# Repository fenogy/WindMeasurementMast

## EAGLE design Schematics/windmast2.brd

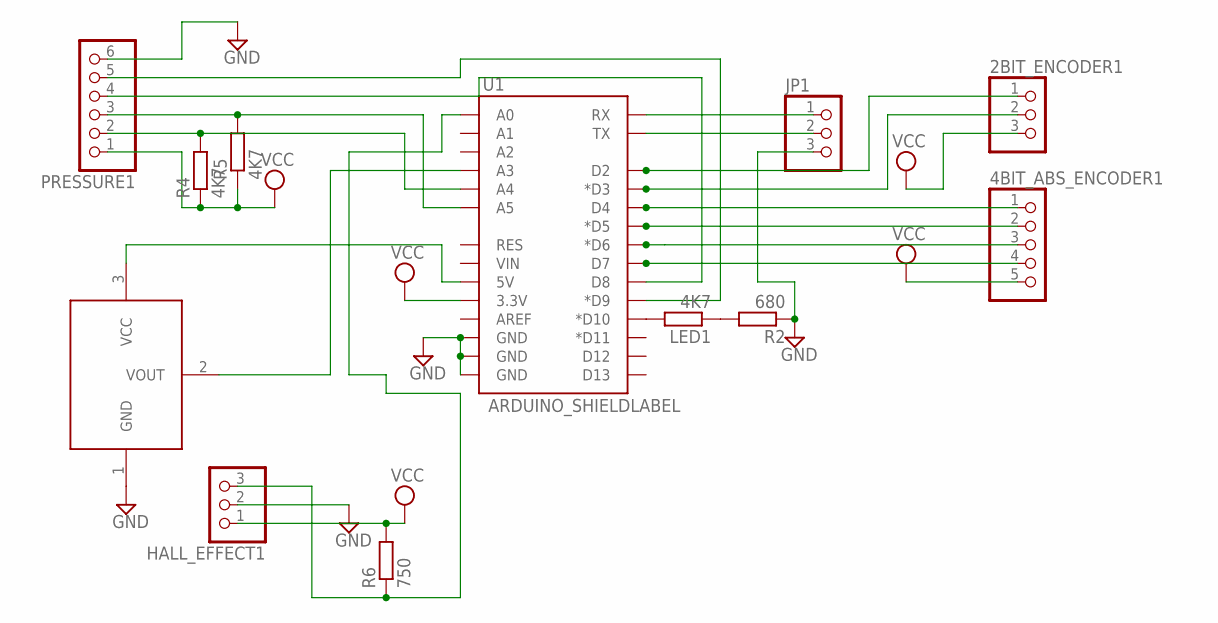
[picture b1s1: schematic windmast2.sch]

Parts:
2BIT_ENCODER1: PINHD-1X3; 1X03
4BIT_ABS_ENCODER1: PINHD-1X5; 1X05
HALL_EFFECT1: PINHD-1X3; 1X03
IC1: LM35; TO92
JP1: PINHD-1X3; 1X03
LED1: 4K7; R0805
PRESSURE1: PINHD-1X6; 1X06
R2: 680; R0805
R4, R5: 4K7; R0805
R6: 750; R0805
U1: ARDUINO_SHIELDLABEL; DUEMILANOVE_SHIELD

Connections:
GND: HALL_EFFECT1.2, IC1.1 (GND), JP1.3, PRESSURE1.6, R2.1, U1.GND@0 (GND), U1.GND@1 (GND), U1.GND@2 (GND)
unnamed: IC1.2 (VOUT), U1.A3
unnamed: IC1.3 (VCC), U1.5V
unnamed: LED1.2, U1.D10 (*D10)
unnamed: LED1.1, R2.2
unnamed: JP1.1, U1.RX
unnamed: JP1.2, U1.TX
unnamed: PRESSURE1.2, R4.2, U1.A4
unnamed: PRESSURE1.3, R5.2, U1.A5
unnamed: PRESSURE1.4, U1.D8
unnamed: PRESSURE1.5, U1.D9 (*D9)
unnamed: 2BIT_ENCODER1.1, U1.D2
unnamed: 2BIT_ENCODER1.2, U1.D3 (*D3)
unnamed: 4BIT_ABS_ENCODER1.1, U1.D4
unnamed: 4BIT_ABS_ENCODER1.2, U1.D5 (*D5)
unnamed: 4BIT_ABS_ENCODER1.3, U1.D6 (*D6)
unnamed: 4BIT_ABS_ENCODER1.4, U1.D7
unnamed: HALL_EFFECT1.3, R6.1, U1.A0
VCC: 2BIT_ENCODER1.3, 4BIT_ABS_ENCODER1.5, HALL_EFFECT1.1, PRESSURE1.1, R4.1, R5.1, R6.2, U1.3.3V

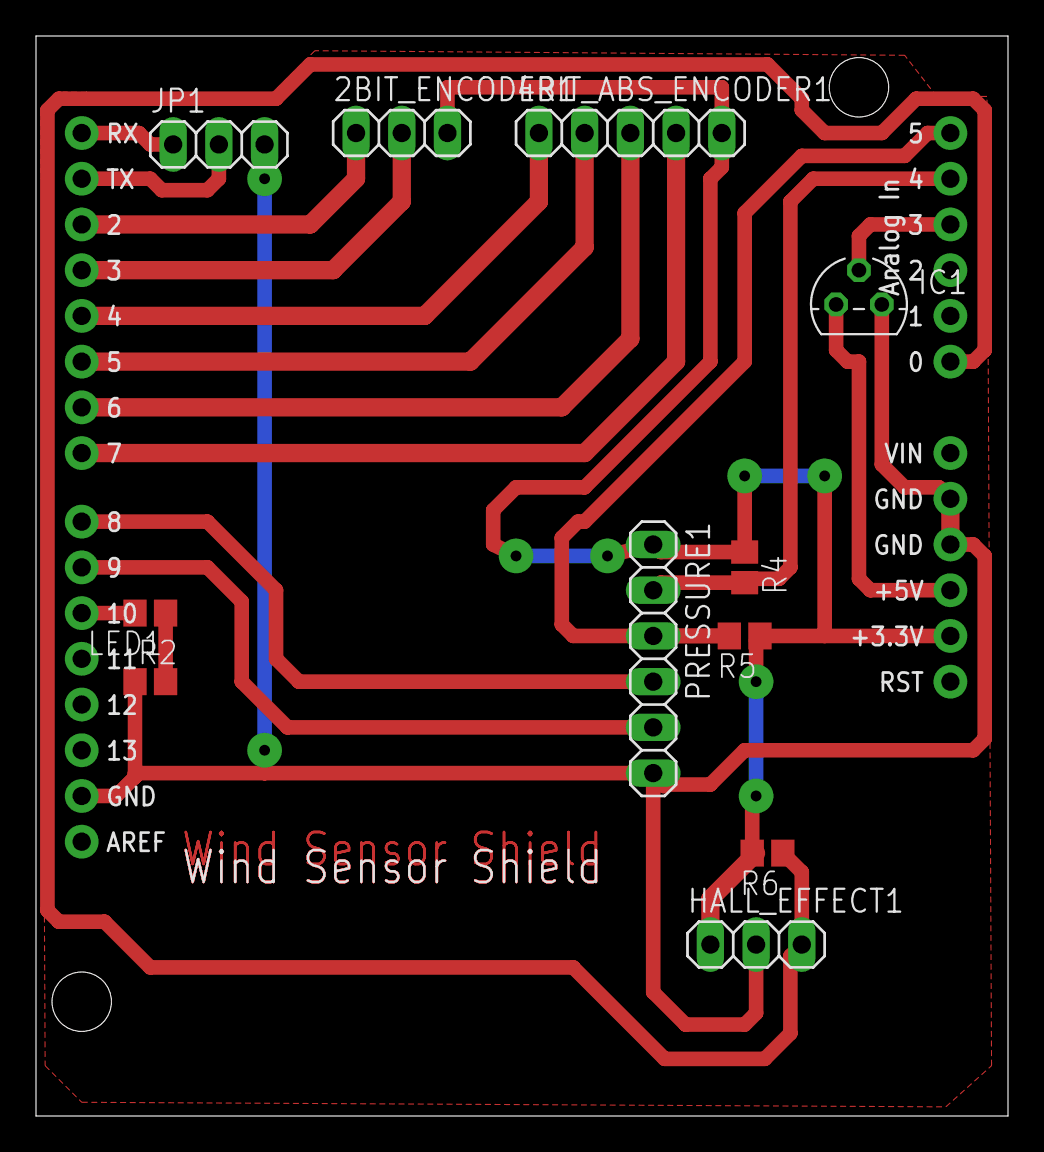
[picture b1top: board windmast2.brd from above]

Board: 2 copper layers, 54.0 x 60.0 mm, 12 parts (0 on the bottom side), 19 nets.

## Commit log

2019-07-06 initial

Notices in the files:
parts and their libraries:
SparkFun-Boards: Licensing: CC v3.0 Share-Alike You are welcome to use this library for commercial purposes.
